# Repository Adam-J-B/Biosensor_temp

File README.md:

Biosensor - Arduino & Eagle Files
=============

Bio-electro chemical sensor project at University of Illinois at Urbana - Champaign.

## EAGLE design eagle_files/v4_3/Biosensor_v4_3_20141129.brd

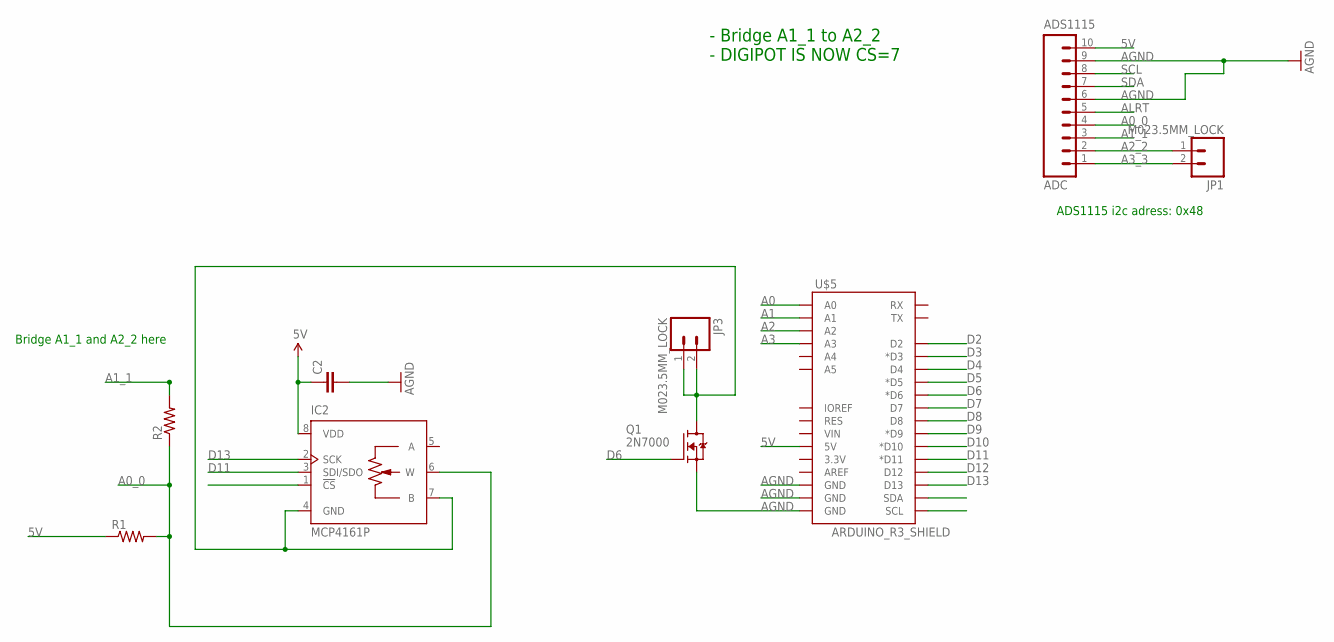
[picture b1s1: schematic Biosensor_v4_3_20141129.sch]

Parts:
ADS1115: ADC; 1X10_LOCK
C2: CAPKIT; CAP-PTH-SMALL-KIT
IC2: MCP4161P; DIL08
JP1, JP3: M023.5MM_LOCK; SCREWTERMINAL-3.5MM-2_LOCK
Q1: 2N7000; TO-92
R1, R2: RESISTORPTH-1/2W; AXIAL-0.5
U$5: ARDUINO_R3_SHIELD; UNO_R3_SHIELD

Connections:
5V: ADS1115.10, C2.1, IC2.8 (VDD), R1.P$1 (1), U$5.5V
A0: U$5.A0
A0_0: ADS1115.4, IC2.6 (W), R1.P$2 (2), R2.P$1 (1)
A1: U$5.A1
A1_1: ADS1115.3, R2.P$2 (2)
A2: U$5.A2
A2_2: ADS1115.2, JP1.1
A3: U$5.A3
A3_3: ADS1115.1, JP1.2
AGND: ADS1115.6, ADS1115.9, C2.2, Q1.1 (S), U$5.GND@0 (GND), U$5.GND@1 (GND), U$5.GND@2 (GND)
ALRT: ADS1115.5
D2: U$5.D2
D3: U$5.D3 (*D3)
D4: U$5.D4
D5: U$5.D5 (*D5)
D6: Q1.2 (G), U$5.D6 (*D6)
D7: IC2.1 (!CS), U$5.D7
D8: U$5.D8
D9: U$5.D9 (*D9)
D10: U$5.D10 (*D10)
D11: IC2.3 (SDI/SDO), U$5.D11 (*D11)
D12: U$5.D12
D13: IC2.2 (SCK), U$5.D13
unnamed: IC2.4 (GND), IC2.7 (B), JP3.1, JP3.2, Q1.3 (D)
SCL: ADS1115.8, U$5.SCL
SDA: ADS1115.7, U$5.SDA

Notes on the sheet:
ADS1115 i2c adress: 0x48
- Bridge A1_1 to A2_2 - DIGIPOT IS NOW CS=7
Bridge A1_1 and A2_2 here

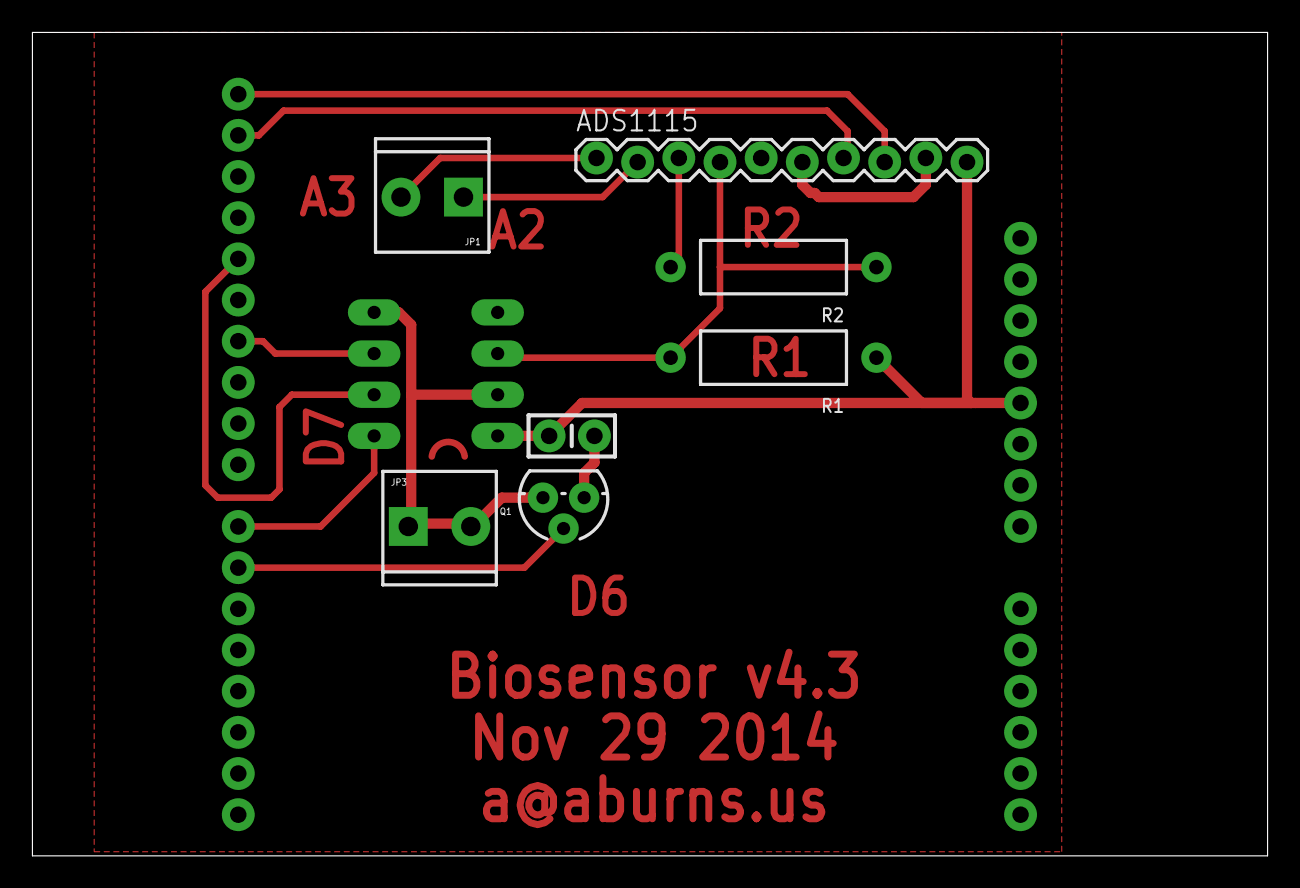
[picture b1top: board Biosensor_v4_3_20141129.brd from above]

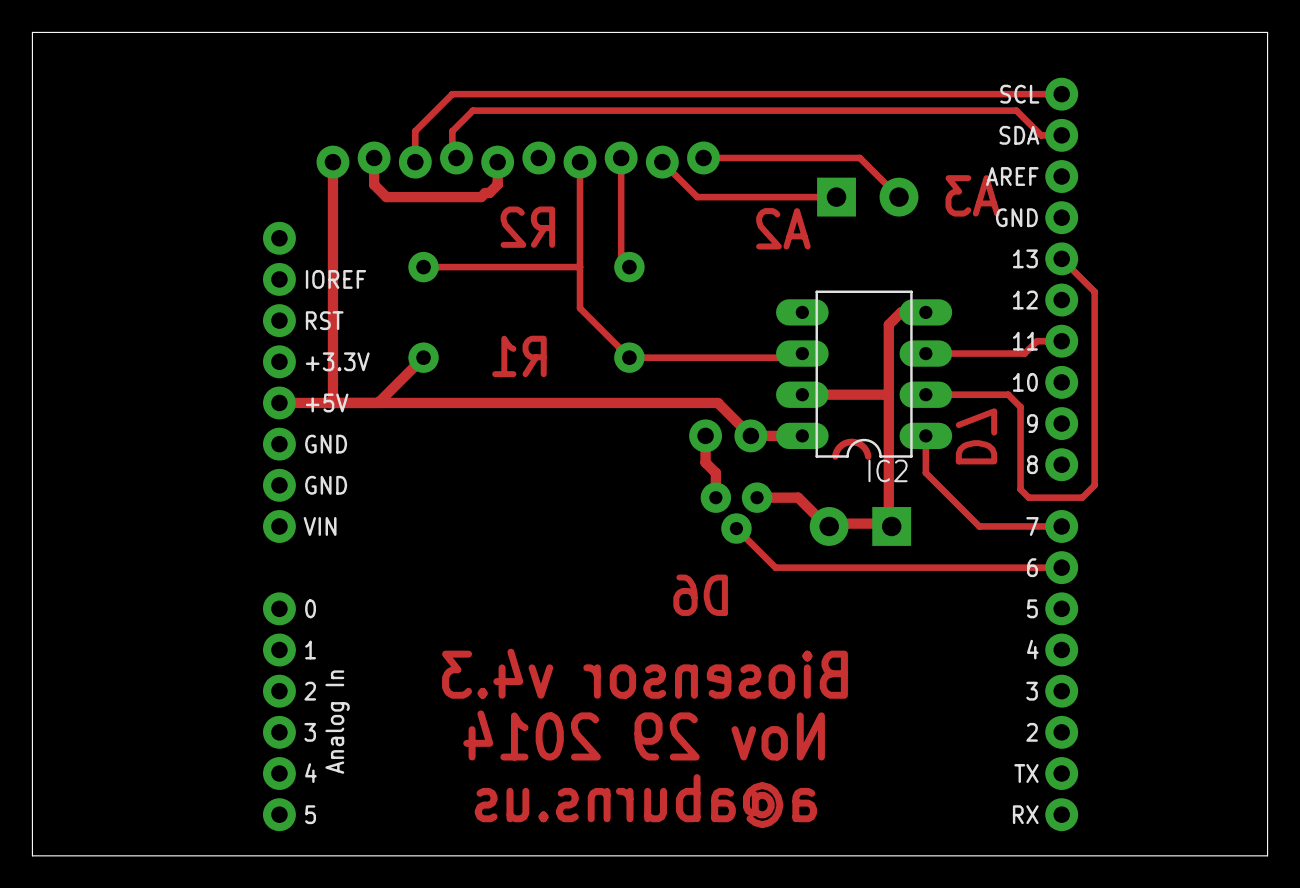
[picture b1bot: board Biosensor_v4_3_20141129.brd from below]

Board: 2 copper layers, 76.2 x 50.8 mm, 9 parts (2 on the bottom side), 13 nets.

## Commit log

2015-03-16 :lollipop: Added .gitattributes & .gitignore files

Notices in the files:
parts and their libraries:
SparkFun-Resistors: Licensing: Creative Commons ShareAlike 4.0 International - https://creativecommons.org/licenses/by-sa/4.0
SparkFun-Connectors: Licensing: CC v3.0 Share-Alike You are welcome to use this library for commercial purposes.
